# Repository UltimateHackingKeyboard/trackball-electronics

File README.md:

Ultimate Hacking Keyboard trackball module
==========================================

Contained are the schematics and board layout KiCad files for the [Ultimate Hacking Keyboard](https://ultimatehackingkeyboard.com/) trackball module.

Make sure to clone this repo with:

`git clone --recursive git@github.com:UltimateHackingKeyboard/trackball-electronics.git`

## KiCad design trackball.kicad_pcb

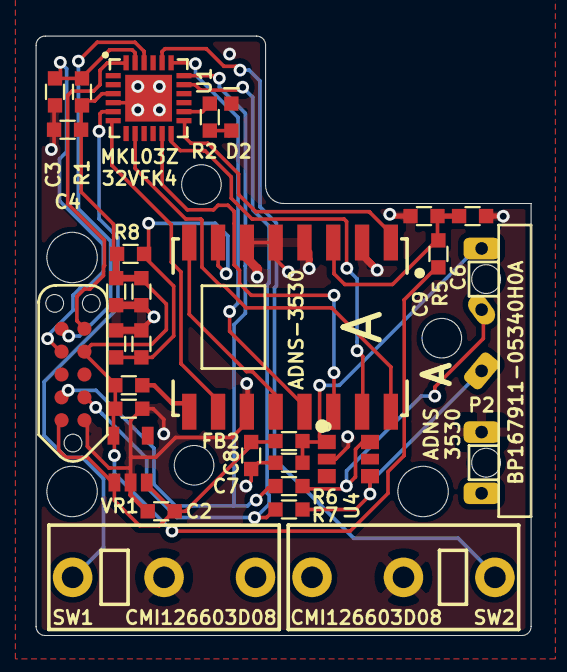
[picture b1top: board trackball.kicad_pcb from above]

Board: 2 copper layers, 27.5 x 33.3 mm, 29 parts (0 on the bottom side), 25 nets.

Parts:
C1, C2, C6, C10, C12: 1uF; SM0603
C3, C4, C7, C8: 0.1uF; SM0603
C5, C9, C11: 10nF; SM0603
D2: LED; SM0603_Diode
FB2: FERRITE_BEAD; SM0603
P1: CONN_10; Tag_Connect_2x5_Header_With_No_Legs_Parallel_Numbering
P2: CONN_5; UHK_Male_Pogo_Pin_v2_trackball
R1: 5.1K; SM0603
R2: 330; SM0603
R3, R5, R8: 5.6; SM0603
R6, R7: 33; SM0603
SW1, SW2: CMI126603D08
U1: MKL03Z32VFK4; QFN-24-1EP_4x4mm_Pitch0.5mm
U2: ADNS-3530
U4: ESD; SC-74-TVS
VR1: MIC5504-3.3YM5; SOT-23-5

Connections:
+3V3: C1.2, C4.2, C5.2, C12.2, P1.7, R1.1, R3.2, R5.2, R8.2, U1.3, VR1.5
+5V: C2.2, C8.2, FB2.2, P1.2, VR1.1, VR1.3
/ADNS_AVDD: C10.2, C11.2, R8.1, U2.10
/ADNS_VDD: C6.2, C9.2, R5.1, U2.14
/LED+: R3.1, U2.8
/LED-: U2.5, U2.9
/MISO: U1.8, U2.1
/MOSI: U1.11, U2.3
/MOTION: U1.19, U2.4
/NCS: U1.13, U2.16
/RESET: C3.2, P1.8, R1.2, U1.23
/SCK: U1.12, U2.2
/SCL: P1.3, R7.1, U1.17
/SCL_BOTTOM: P2.3, R7.2, U4.4
/SDA: P1.4, R6.1, U1.18
/SDA_BOTTOM: P2.2, R6.2, U4.5
/SHTDWN: U1.6, U2.7
/SW1: SW1.1, U1.5
/SW2: SW2.1, U1.20
/SWDCLK: P1.10, U1.22
/SWDIO: P1.9, U1.24
/TEST_LED: R2.2, U1.14
/TEST_LED_R: D2.2, R2.1
/VCC_BOTTOM: C7.2, FB2.1, P2.1, U4.1
GND: C1.1, C2.1, C3.1, C4.1, C5.1, C6.1, C7.1, C8.1, C9.1, C10.1, C11.1, C12.1, D2.1, P1.1, P2.4, SW1.2, SW2.2, U1.4, U1.25, U2.6, U2.11, U2.12, U2.13, U2.15, U4.2, VR1.2

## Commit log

2019-07-03 Add gitignore.
2019-07-03 Import mechanical PCB.
2019-07-03 Add components to the board.
2019-07-03 Add keepout areas.
2019-07-05 Add sch to project.
2019-07-07 Improve silk screen.
2019-07-07 Update description
2019-07-08 Updated library reference.
2019-07-08 Add submodule.
2019-07-08 Manual merge trick.
2019-07-08 Footprint library references modified.
2019-07-08 Components added.
2019-07-08 Update contour.
2019-07-09 Update library reference.
2019-07-09 First final version without test points.
2019-07-10 Remove test points.
2019-07-10 Visible values on silkscreen.
2019-07-15 Add libs readme.
2019-07-17 Change UPA header pinout.
2019-07-21 Update microswitch footprints.
2019-08-05 Improve silk screen. Feature 5.6 instead of 5R6.
2019-08-05 Update ADNS-3530 footprint.
2019-08-05 Bump version number to 1.0.0
2019-08-05 Ignore backup and cache files.
2019-08-05 Add netlist.
2019-08-05 Ignore generated bom.
2019-08-05 Make microswitch values consistent for them to show up as similar BOM components.
2019-08-05 Display optical sensor and microswitch part number on the silk screen.
2019-08-07 Display part number for the pogo pin connector.
2019-08-07 Add UHK logo.
2019-08-09 Bump version number to 1.1.0
2019-08-09 Add UPA14 text.
2019-08-09 Enable additional layers.
2019-08-10 Rename UPA14 to UPA10.
2019-08-15 Add clearances around mechanical holes.
2019-08-16 Make pogo pin through hole, make logo virtual, make ESD text visible.
2019-09-10 Update ADNS-3530 footprint and reconnect pads.
2019-10-27 Update microswitch and ADNS modules.
2019-10-27 Add orientation marker circle for the ESD suppressor.
2019-10-27 Bump version number to 1.2.0
2019-10-27 Ignore *.sch-bak
2019-10-27 Show LED value instead of reference designator.
2019-10-27 Update LED module.
2019-12-09 Set the size of all label text size to 0.04 inch.
2019-12-09 Make the size of all labels 0.04 inch.
2020-01-24 Make the test LED and its resistor virtual.
2020-03-05 Add license.
2020-03-15 Fix sensor position.
2020-03-15 Update sensor footprint.
2020-03-15 Add additional silk screen content for the sensor.
2020-04-05 Disconnect pin 5 of the pogo pin connector.
2020-04-12 Update Kailh microswitches.
2020-05-16 Add readme.
2020-05-16 Update the submodule URL of ugl-kicad-lib
2020-05-17 Replace resistors from 4.7K to 5.1K and from 47 to 33 ohms.
2020-05-17 Remove redudant C13.
2020-05-17 Remove redundant R4.
2020-05-17 Fix schematic around R5 and R8.
2020-05-18 Update board based on CAD.
2020-05-18 Bump version to 1.3.0
2020-06-06 Reroute board on a shrinked area.
2020-06-06 Don't route tracks on the part of the board that will be removed.
2020-06-06 Use 8 mil tracks all around.
2020-06-06 Move the MCU closer to the center of the board.
2020-06-06 Minimize board outline.
2020-06-06 Add back logo to the board.
2020-06-06 Spruce up silk screen.
2020-06-06 Rename microswitch reference designators to SW1 and SW2.
2020-06-06 Move test LED components farther from the nearby boss.
2020-06-06 Tweak pogo pin pad.
2020-06-06 Make the width of the upper region of the PCB 12.75 mm.
2020-06-06 Set the height of the board precisely to 33.3 mm.
2020-06-06 Tweak silk screen.
2020-06-06 Don't cover R2 and D2 with paste.
2020-06-06 Resolve DRC issue by repositioning C8.
2020-06-06 Clean up minor silk screen issues.
2020-06-06 Bump board version to 1.4.0
2020-06-10 Capitalize UGL schematic library name.
2020-06-10 Capitalize UGL library name for the board.
2020-06-11 Tweak plot parameters.
2020-06-19 Update ADNS-3530 module.
2020-09-07 Make silk screen easier to read and improve polarization marks.
2020-10-13 Improve silk screen for AOI.
2020-10-13 Bump version to 1.4.1
2020-10-15 Move away tracks from the keepout areas of screws as much as possible.
2020-10-15 Bump version to 1.5.0
2021-11-15 Update submodule path.
